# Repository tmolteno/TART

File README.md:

# Transient Array Radio Telescope

This repository has been ARCHIVED. It has been split into many smaller repositories under the tart-telescope organization.
see (https://github.com/tart-telescope) for details

The [Transient Array Radio Telescope](https://en.wikipedia.org/wiki/Transient_Array_Radio_Telescope) (TART) is a low-cost 24-element aperture synthesis array
developed by the [Elec Research Group](http://elec.ac.nz) at the University of Otago

 ![All-sky image from a TART telescope][tart_image] 

The TART software and hardware designs are released as open-source designs and are
licensed under the GPL v3.

The authors of the first version of the TART are Tim Molteno, Charles Shaw, Max 
Scheel and Phil Brown. Enquries about the TART should be addressed to Tim Molteno (tim@elec.ac.nz). 

[Connect to our development radio telescope here](https://tart.elec.ac.nz "Online Telescopes")

## Hardware

The TART hardware is designed using a combination of KiCAD (newest boards) and
CadSoft's Eagle package. These designs are located in the [hardware](hardware/README.md) folder. 

## Firmware

The TART uses an FPGA to synchronize data from each receiver. The code for this in the 
Verilog language is in the [hardware/FPGA](hardware/FPGA/README.md) directory

## Installation

See the  [Installation Instructions](INSTALL.md) file for more detail on installation.

[tart_image]: https://github.com/tmolteno/TART/blob/master/doc/img/tart_image.jpg "TART All-Sky Image"

## Telescope API documentation

The [Telescope API documentation](https://tart.elec.ac.nz/doc/) describes how the TART is controlled via the network for configration and data retrieval.

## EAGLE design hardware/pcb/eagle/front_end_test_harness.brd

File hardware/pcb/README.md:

At the moment TART consists of three different PCBs:

1. (24x) Radio module (RF front end)
2. (4x) Radio hub module (jitter cleaner, power supply, 485 transceiver and base for 6 Radio modules)
3. (1x) Base station module (485 transceiver, oscillator, power supply, host for acquisition FPGA and Raspberry Pi)

base_station, radio_hub_module and radio_module are the original designs used for all currently built up TART's (as of Feb 2019). The base_station folder is a KIcad project, while radio_hub_module and radio_module are created in Eagle PCB.

The *201902 folder are the above converted and updated to KIcad 5 projects.

BOM html and CSV files are included. These are generated by the github.com:SchrodingersGat/KiBoM.git plugin.

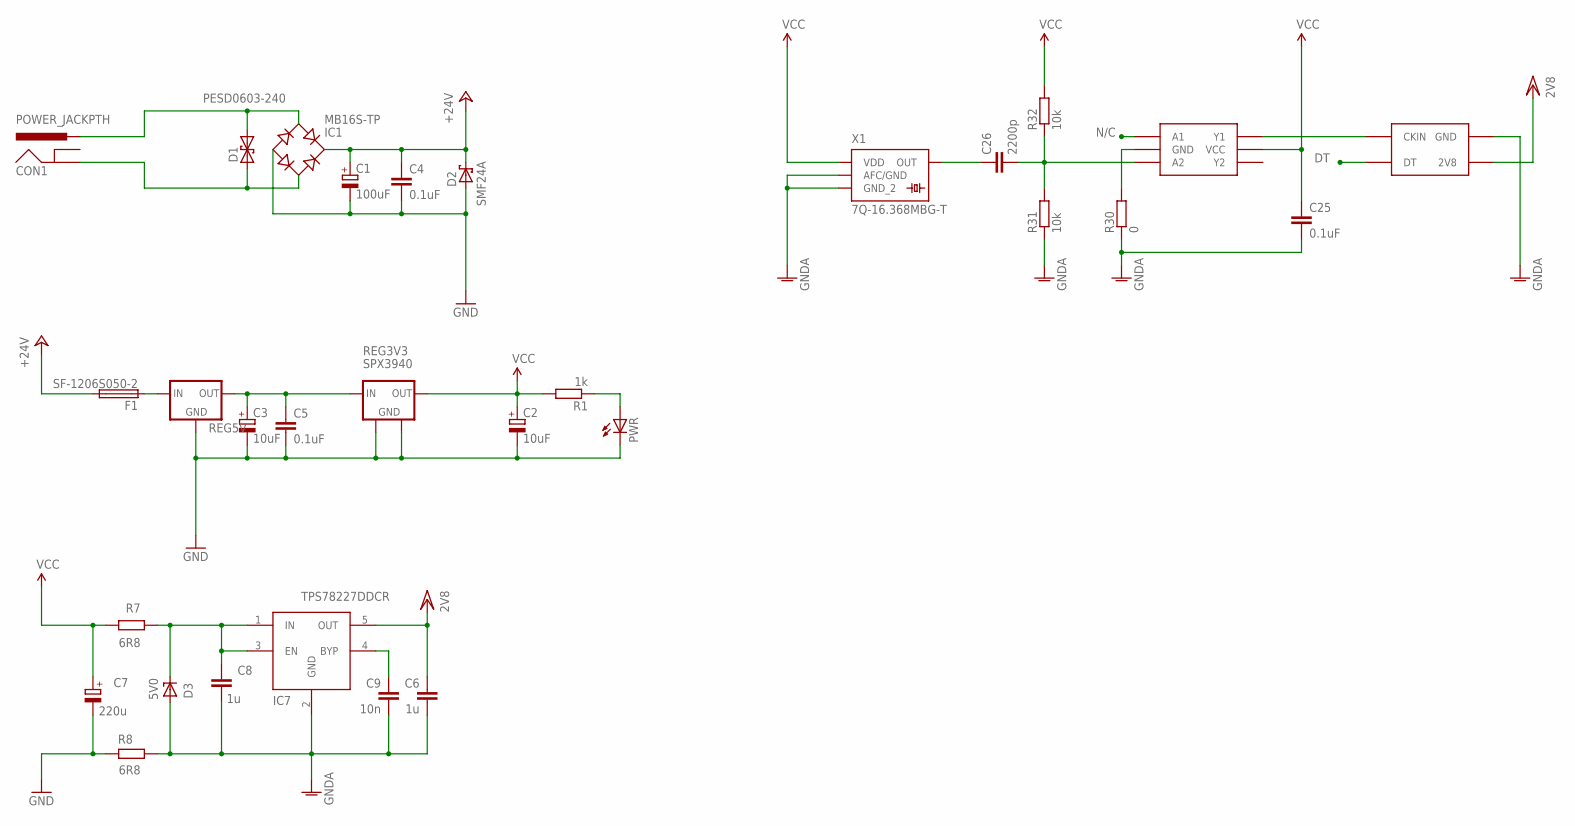
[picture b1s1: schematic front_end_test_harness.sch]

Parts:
C1: 100uF; E5-10,5
C2: 10uF; E2-5
C3: 10uF; E5-10,5
C4, C5: 0.1uF; C0805
C6, C8: 1u; C0603
C7: 220u; C1210
C9: 10n; C0603
C25: 0.1uF; C0603
C26: 2200p; C0603
CON1: POWER_JACKPTH; POWER_JACK_PTH
D1: PESD0603-240; D0603
D2: SMF24A; SOD123
D3: 5V0; SOD523
F1: SF-1206S050-2; F1206
IC1: MB16S-TP; SOIC-4
IC7: TPS78227DDCR; SOT23-5
IC26: NC7WZ16P6X
PWR: LEDCHIPLED_0805; CHIPLED_0805
R1: 1k; R0603
R7, R8: 6R8; R0805
R30: 0; R0603
R31, R32: 10k; R0603
REG3V3: SPX3940; SOT223
REG5V: V_REG_OKI-78SRSINK; TO220-IGO
U$2: TEST_HARNESS
X1: 7Q-16.368MBG-T; 4-SMD

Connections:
+2V8: C6.1, IC7.5 (OUT), U$2.2V8@11 (2V8), U$2.2V8@15 (2V8), U$2.2V8@16 (2V8)
+5V: C3.+, C5.1, REG3V3.1 (IN), REG5V.OUT
+24V: C1.+, C4.1, D2.C, F1.2, IC1.+
A2: C26.2, IC26.P$3 (A2), R31.2, R32.1
BYP: C9.1, IC7.4 (BYP)
CLK: IC26.P$6 (Y1), U$2.CKIN@13 (CKIN)
DT: U$2.DT@12 (DT)
GNDA: C6.2, C8.2, C9.2, C25.2, D3.A, IC7.2 (GND), R8.1, R30.1, R31.1, U$2.GND@1 (GND), U$2.GND@2 (GND), U$2.GND@3 (GND), U$2.GND@4 (GND), U$2.GND@5 (GND), U$2.GND@6 (GND), U$2.GND@7 (GND), U$2.GND@8 (GND), U$2.GND@9 (GND), U$2.GND@11 (GND), U$2.GND@14 (GND), X1.PAD_1 (AFC/GND), X1.PAD_2 (GND_2)
GNDINT: C1.-, C2.-, C3.-, C4.2, C5.2, C7.2 (-), D2.A, IC1.-, PWR.C, R8.2, REG3V3.2 (GND), REG3V3.4 (GND), REG5V.GND
unnamed: PWR.A, R1.1
unnamed: F1.1, REG5V.IN
unnamed: IC26.P$2 (GND), R30.2
unnamed: CON1.PWR, D1.2, IC1.~1 (AC1)
unnamed: CON1.GND, D1.1, IC1.~2 (AC2)
unnamed: C26.1, X1.PAD_3 (OUT)
N/C: IC26.P$1 (A1)
REG2V7IN: C8.1, D3.C, IC7.1 (IN), IC7.3 (EN), R7.1
VCC: C2.+, C7.1 (+), C25.1, IC26.P$5 (VCC), R1.2, R7.2, R32.2, REG3V3.3 (OUT), X1.PAD_4 (VDD)

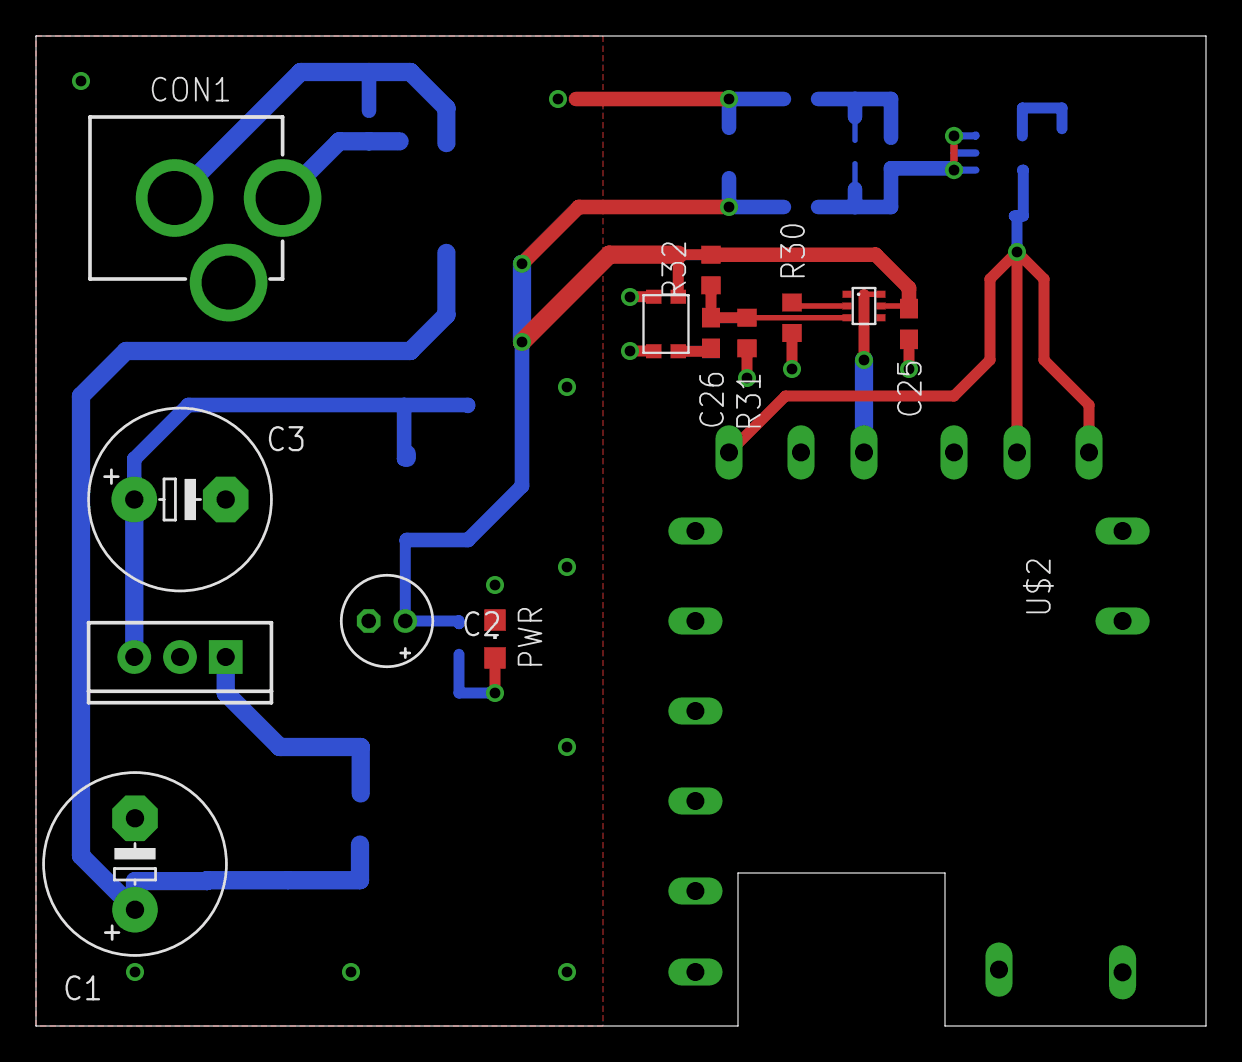
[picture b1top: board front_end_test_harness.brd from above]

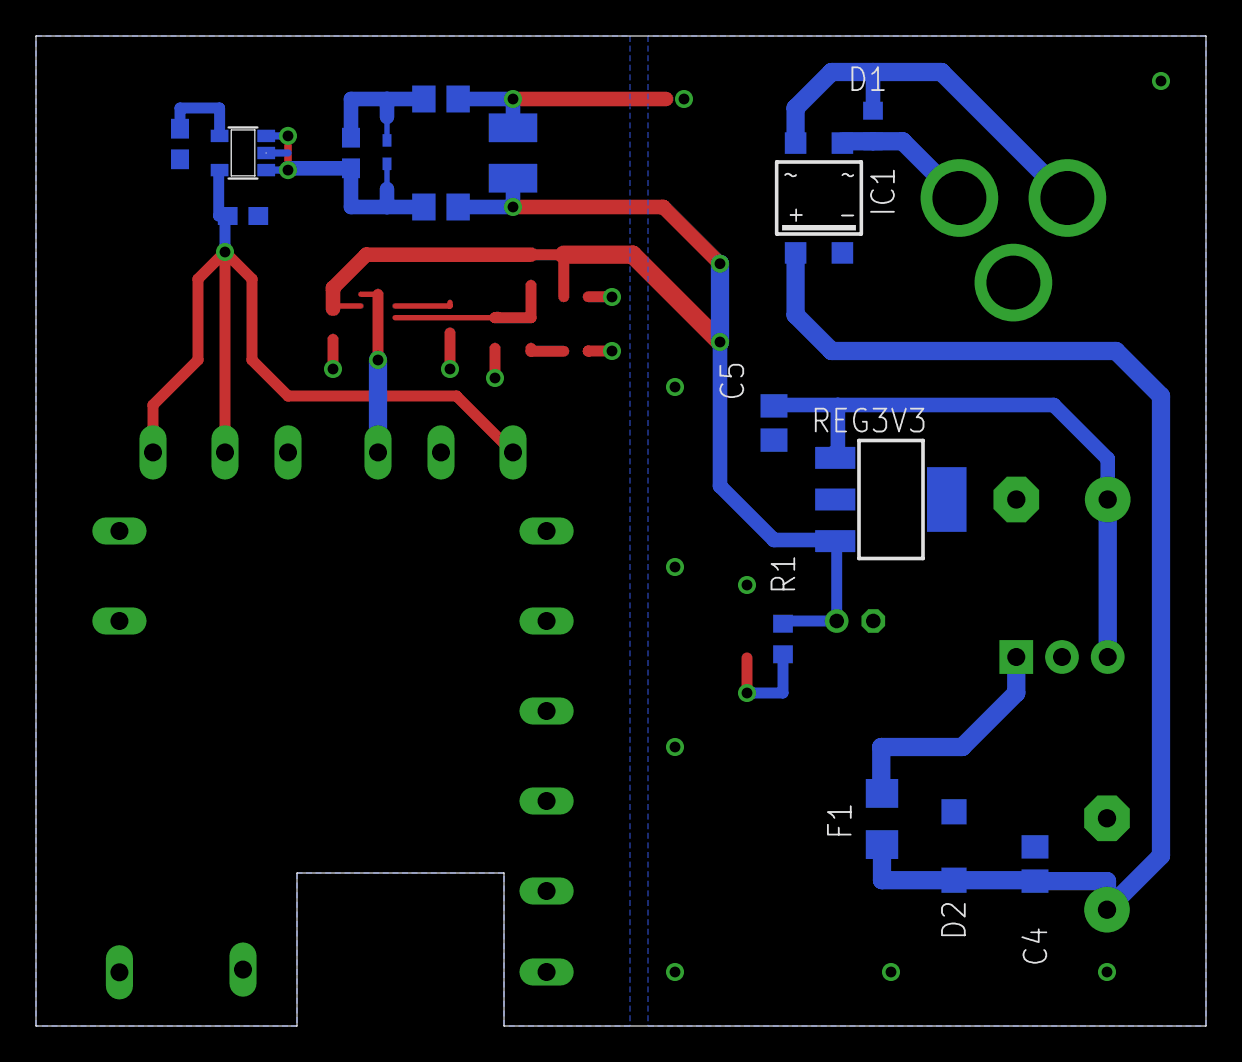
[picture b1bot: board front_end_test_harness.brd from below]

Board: 2 copper layers, 65.0 x 55.0 mm, 30 parts (16 on the bottom side), 16 nets.

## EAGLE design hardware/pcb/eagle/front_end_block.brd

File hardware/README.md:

# TART Hardware Description

The TART telescope consists of three major components.

* Radio Front End Module
* Radio Hub Module
* Base Station

## Radio Front End

The radio front end is a low-noise [radio](https://datasheets.maximintegrated.com/en/ds/MAX2769B.pdf) that digitizes the incoming signal at a sample rate of 16.368 MHz. An external clock input is used to synchronize the sampling. A full tart telescope consists of 24 radio front end modules arranged into four 'Tiles'

![TART GPS L1 radio front end][radio_front_end_image]

## Radio Hub Module

A radio hub module controls six radio front ends. It is responsible for generating low-noise power, 
and removing jitter from the main system clock (generated from the base station).
The radio hub distributes this clean clock to each of the radio front end modules. The data from each radio is converted to RS422 differential signaling and fed back down Cat-6 UTP cabling back to the basestation. 

![Radio Hub Module][radio_hub_image]

This image shows a radio hub with six radio front end modules mounted.

## Base Station

The basestation is responsible for three main tasks.

* Clock & Power Generation
* Data reception
* Data resynchronization and buffering
* Storage and Upload

The clock and power generation hardware is described in the pcb/base_station folder.

The data resynchronization and buffering is performed using an FPGA. The hardware and Verilog source for this are described
int the folder FPGA.

The Data storage and upload are managed by a raspberry pi computer running Linux. The software for operating this computer is described in the software directory in the main TART folder.

![Radio Telescope Basestation][basestation_image]

[radio_front_end_image]: https://github.com/tmolteno/TART/blob/master/doc/img/radio_module.png "TART Radio Module"
[radio_hub_image]: https://github.com/tmolteno/TART/blob/master/doc/img/radio_hub_photo.jpg "TART Radio Hub"
[basestation_image]: https://github.com/tmolteno/TART/blob/master/doc/img/control_board_photo.png "TART Basestation"

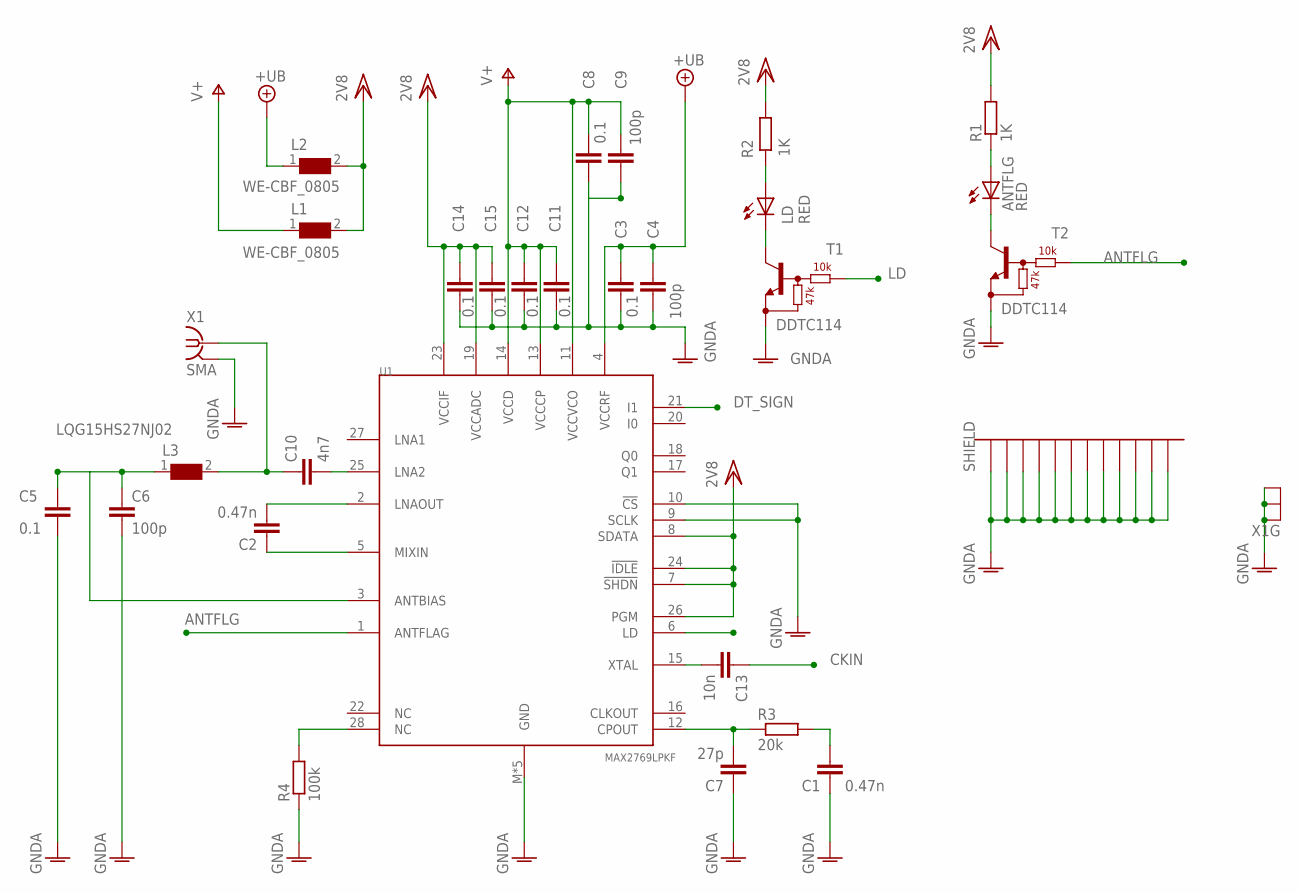
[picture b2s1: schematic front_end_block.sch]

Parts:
ANTFLG: RED; CHIP-LED0603
C1: 0.47n; C0603
C2: 0.47n; C0402
C3, C8, C11, C12, C15: 0.1; C0402
C4, C6, C9: 100p; C0402
C5, C14: 0.1; C0603
C7: 27p; C0402
C10: 4n7; C0402
C13: 10n; C0402
L1, L2: WE-CBF_0805; 0805
L3: LQG15HS27NJ02; 0402
LD: RED; CHIP-LED0603
R1, R2: 1K; R0402
R3: 20k; R0402
R4: 100k; R0402
S2: BMIS-202
T1, T2: DDTC114; SOT323-R_INFINEON
U1: MAX2769LPKF; QFN28LPKF
X1: SMA; J502-ND-142-0701-801/806

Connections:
+UB: C3.1, C4.1, L2.1, U1.4 (VCCRF)
ANTFLG: T2.1 (B), U1.1 (ANTFLAG)
CKIN: C13.1
DT_SIGN: U1.21 (I1)
GNDA: C1.1, C3.2, C4.2, C5.2, C6.2, C7.1, C8.2, C9.2, C11.2, C12.2, C14.2, C15.2, R4.1, S2.P$1, S2.P$2, S2.P$3, S2.P$4, S2.P$5, S2.P$6, S2.P$7, S2.P$8, S2.P$9, S2.P$10, S2.P$11, S2.P$12, T1.2 (E), T2.2 (E), U1.9 (SCLK), U1.10 (!CS), U1.M (GND), U1.P$4 (GND), U1.P$6 (GND), U1.P$7 (GND), U1.P$9 (GND), X1.G@1 (GND), X1.G@2 (GND), X1.G@3 (GND), X1.G@4 (GND)
LD: T1.1 (B), U1.6 (LD)
LNA2: C10.2, U1.25 (LNA2)
LNAOUT: C2.2, U1.2 (LNAOUT)
MIXIN: C2.1, U1.5 (MIXIN)
unnamed: C7.2, R3.1, U1.12 (CPOUT)
unnamed: C1.2, R3.2
unnamed: C5.1, C6.1, L3.1, U1.3 (ANTBIAS)
unnamed: ANTFLG.A, R1.1
unnamed: ANTFLG.C, T2.3 (C)
unnamed: LD.A, R2.1
unnamed: LD.C, T1.3 (C)
unnamed: R4.2, U1.28 (NC)
unnamed: C10.1, L3.2, X1.1
V+: C8.1, C9.1, C11.1, C12.1, L1.1, U1.11 (VCCVCO), U1.13 (VCCCP), U1.14 (VCCD)
VCC/2: C14.1, C15.1, L1.2, L2.2, R1.2, R2.2, U1.7 (!SHDN), U1.8 (SDATA), U1.19 (VCCADC), U1.23 (VCCIF), U1.24 (!IDLE), U1.26 (PGM)
XTAL: C13.2, U1.15 (XTAL)

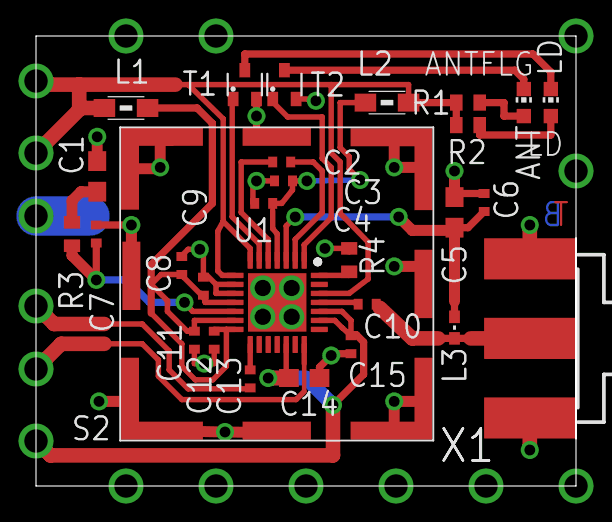
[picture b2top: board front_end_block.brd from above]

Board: 2 copper layers, 30.0 x 25.0 mm, 29 parts (0 on the bottom side), 19 nets.

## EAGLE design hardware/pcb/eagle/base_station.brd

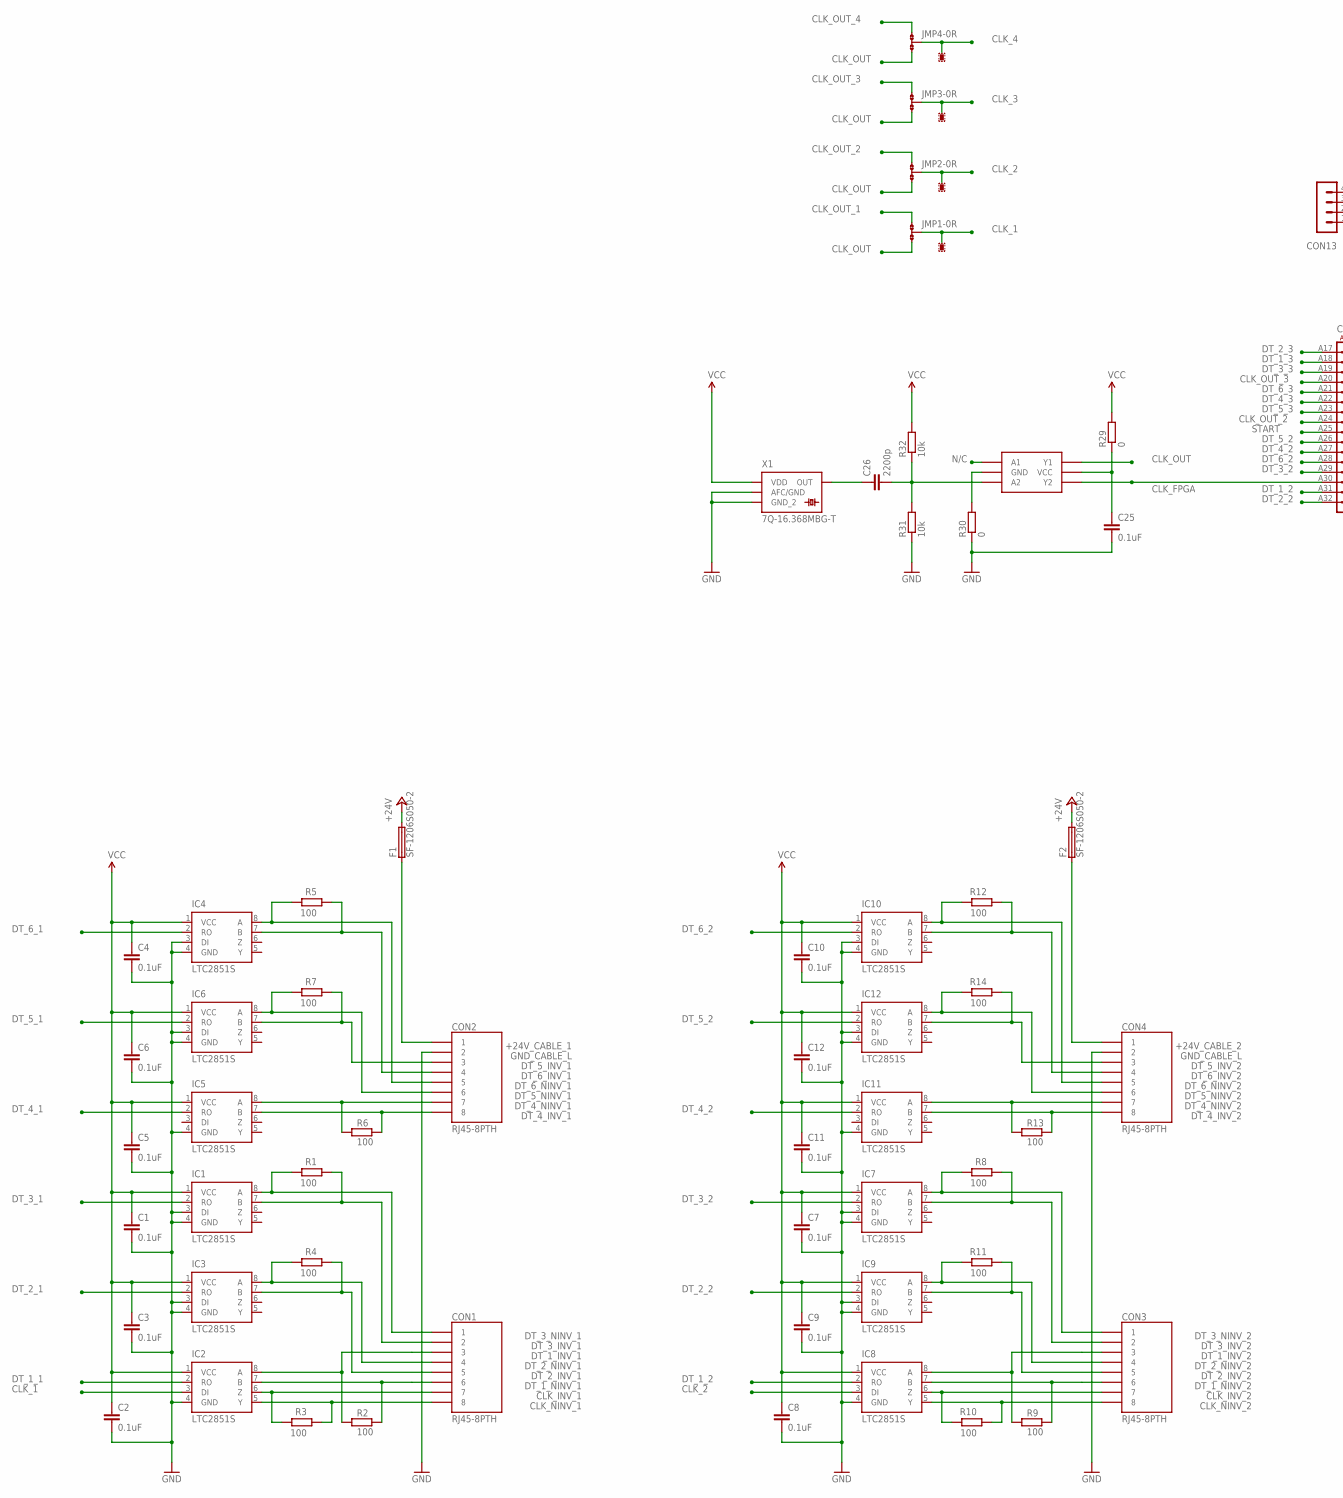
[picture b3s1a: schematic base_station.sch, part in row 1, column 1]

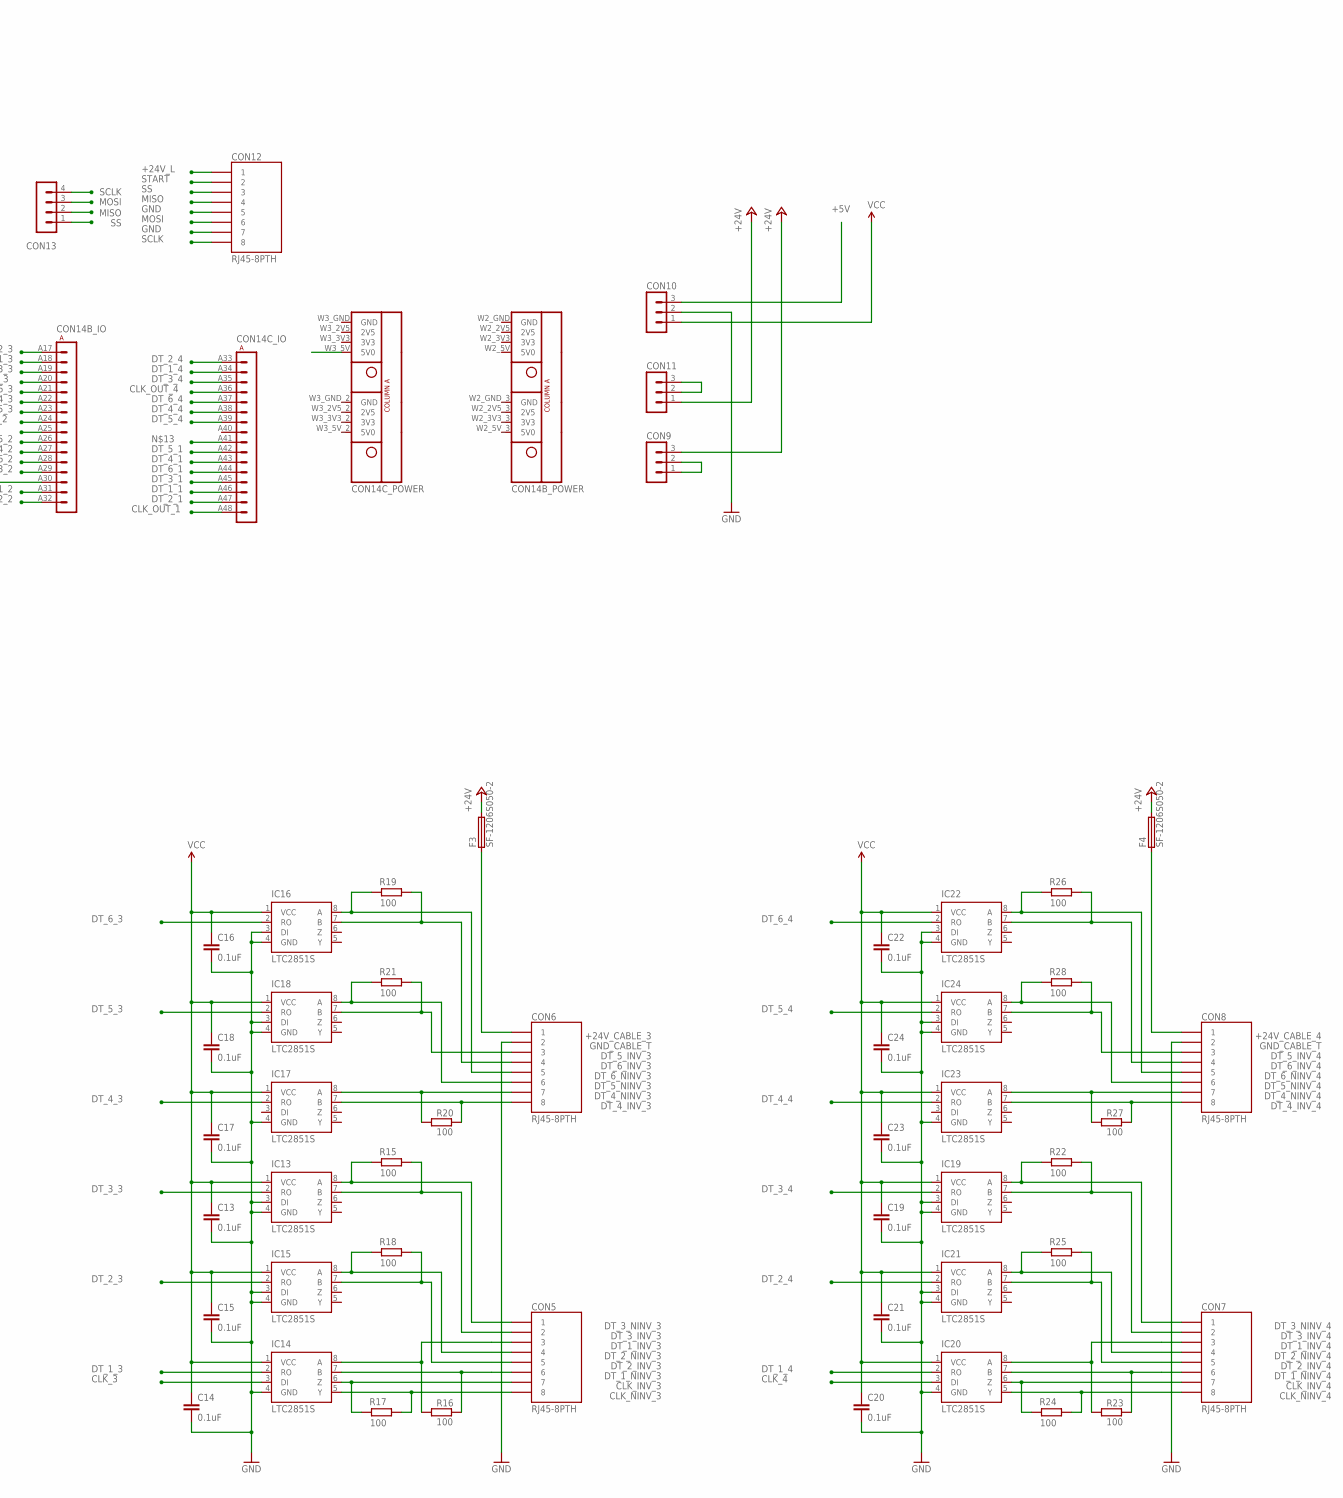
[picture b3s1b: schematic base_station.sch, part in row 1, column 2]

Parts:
C1, C2, C3, C4, C5, C6, C7, C8, C9, C10, C11, C12, C13, C14, C15, C16, C17, C18, C19, C20, C21, C22, C23, C24, C25: 0.1uF; C0603
C26: 2200p; C0603
CON1, CON2, CON3, CON4, CON5, CON6, CON7, CON8, CON12: RJ45-8PTH; RJ45-8
CON9, CON10, CON11: MA03-1
CON13: WING4; WINGSIDE_4BIT
CON14: MEGAWING_HALF_P1; MEGAWING_HALF_NOHOLES_P1
F1, F2, F3, F4: SF-1206S050-2; F1206
IC1, IC2, IC3, IC4, IC5, IC6, IC7, IC8, IC9, IC10, IC11, IC12, IC13, IC14, IC15, IC16, IC17, IC18, IC19, IC20, IC21, IC22, IC23, IC24: LTC2851S; SOIC8
IC26: NC7WZ16P6X
JMP1, JMP2, JMP3, JMP4: 0R-JUMPA; A0R-JMP
R1, R2, R3, R4, R5, R6, R7, R8, R9, R10, R11, R12, R13, R14, R15, R16, R17, R18, R19, R20, R21, R22, R23, R24, R25, R26, R27, R28: 100; R0603
R29, R30: 0; R0603
R31, R32: 10k; R0603
X1: 7Q-16.368MBG-T; 4-SMD

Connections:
+5V: CON10.3, CON14.W3_5V (5V0)
+24V_CABLE_1: CON2.1, F1.1
+24V_CABLE_2: CON4.1, F2.1
+24V_CABLE_3: CON6.1, F3.1
+24V_CABLE_4: CON8.1, F4.1
+24V_L: CON9.3, CON12.1, F1.2, F2.2
+24V_T: CON11.1, F3.2, F4.2
CLK_1: IC2.3 (DI), JMP1.2
CLK_2: IC8.3 (DI), JMP2.2
CLK_3: IC14.3 (DI), JMP3.2
CLK_4: IC20.3 (DI), JMP4.2
CLK_FPGA: CON14.A30 (A14), IC26.P$4 (Y2)
CLK_INV_1: CON1.7, IC2.6 (Z), R3.2
CLK_INV_2: CON3.7, IC8.6 (Z), R10.2
CLK_INV_3: CON5.7, IC14.6 (Z), R17.2
CLK_INV_4: CON7.7, IC20.6 (Z), R24.2
CLK_NINV_1: CON1.8, IC2.5 (Y), R3.1
CLK_NINV_2: CON3.8, IC8.5 (Y), R10.1
CLK_NINV_3: CON5.8, IC14.5 (Y), R17.1
CLK_NINV_4: CON7.8, IC20.5 (Y), R24.1
CLK_OUT: IC26.P$6 (Y1), JMP1.3, JMP2.3, JMP3.3, JMP4.3
CLK_OUT_1: CON14.A48 (A16), JMP1.1
CLK_OUT_2: CON14.A24 (A8), JMP2.1
CLK_OUT_3: CON14.A20 (A4), JMP3.1
CLK_OUT_4: CON14.A36 (A4), JMP4.1
DT_1_1: CON14.A46 (A14), IC2.2 (RO)
DT_1_2: CON14.A31 (A15), IC8.2 (RO)
DT_1_3: CON14.A18 (A2), IC14.2 (RO)
DT_1_4: CON14.A34 (A2), IC20.2 (RO)
DT_1_INV_1: CON1.3, IC2.8 (A), R2.1
DT_1_INV_2: CON3.3, IC8.8 (A), R9.1
DT_1_INV_3: CON5.3, IC14.8 (A), R16.1
DT_1_INV_4: CON7.3, IC20.8 (A), R23.1
DT_1_NINV_1: CON1.6, IC2.7 (B), R2.2
DT_1_NINV_2: CON3.6, IC8.7 (B), R9.2
DT_1_NINV_3: CON5.6, IC14.7 (B), R16.2
DT_1_NINV_4: CON7.6, IC20.7 (B), R23.2
DT_2_1: CON14.A47 (A15), IC3.2 (RO)
DT_2_2: CON14.A32 (A16), IC9.2 (RO)
DT_2_3: CON14.A17 (A1), IC15.2 (RO)
DT_2_4: CON14.A33 (A1), IC21.2 (RO)
DT_2_INV_1: CON1.5, IC3.7 (B), R4.1
DT_2_INV_2: CON3.5, IC9.7 (B), R11.1
DT_2_INV_3: CON5.5, IC15.7 (B), R18.1
DT_2_INV_4: CON7.5, IC21.7 (B), R25.1
DT_2_NINV_1: CON1.4, IC3.8 (A), R4.2
DT_2_NINV_2: CON3.4, IC9.8 (A), R11.2
DT_2_NINV_3: CON5.4, IC15.8 (A), R18.2
DT_2_NINV_4: CON7.4, IC21.8 (A), R25.2
DT_3_1: CON14.A45 (A13), IC1.2 (RO)
DT_3_2: CON14.A29 (A13), IC7.2 (RO)
DT_3_3: CON14.A19 (A3), IC13.2 (RO)
DT_3_4: CON14.A35 (A3), IC19.2 (RO)
DT_3_INV_1: CON1.2, IC1.7 (B), R1.1
DT_3_INV_2: CON3.2, IC7.7 (B), R8.1
DT_3_INV_3: CON5.2, IC13.7 (B), R15.1
DT_3_INV_4: CON7.2, IC19.7 (B), R22.1
DT_3_NINV_1: CON1.1, IC1.8 (A), R1.2
DT_3_NINV_2: CON3.1, IC7.8 (A), R8.2
DT_3_NINV_3: CON5.1, IC13.8 (A), R15.2
DT_3_NINV_4: CON7.1, IC19.8 (A), R22.2
DT_4_1: CON14.A43 (A11), IC5.2 (RO)
DT_4_2: CON14.A27 (A11), IC11.2 (RO)
DT_4_3: CON14.A22 (A6), IC17.2 (RO)
DT_4_4: CON14.A38 (A6), IC23.2 (RO)
DT_4_INV_1: CON2.8, IC5.7 (B), R6.2
DT_4_INV_2: CON4.8, IC11.7 (B), R13.2
DT_4_INV_3: CON6.8, IC17.7 (B), R20.2
DT_4_INV_4: CON8.8, IC23.7 (B), R27.2
DT_4_NINV_1: CON2.7, IC5.8 (A), R6.1
DT_4_NINV_2: CON4.7, IC11.8 (A), R13.1
DT_4_NINV_3: CON6.7, IC17.8 (A), R20.1
DT_4_NINV_4: CON8.7, IC23.8 (A), R27.1
DT_5_1: CON14.A42 (A10), IC6.2 (RO)
DT_5_2: CON14.A26 (A10), IC12.2 (RO)
DT_5_3: CON14.A23 (A7), IC18.2 (RO)
DT_5_4: CON14.A39 (A7), IC24.2 (RO)
DT_5_INV_1: CON2.3, IC6.7 (B), R7.1
DT_5_INV_2: CON4.3, IC12.7 (B), R14.1
DT_5_INV_3: CON6.3, IC18.7 (B), R21.1
DT_5_INV_4: CON8.3, IC24.7 (B), R28.1
DT_5_NINV_1: CON2.6, IC6.8 (A), R7.2
DT_5_NINV_2: CON4.6, IC12.8 (A), R14.2
DT_5_NINV_3: CON6.6, IC18.8 (A), R21.2
DT_5_NINV_4: CON8.6, IC24.8 (A), R28.2
DT_6_1: CON14.A44 (A12), IC4.2 (RO)
DT_6_2: CON14.A28 (A12), IC10.2 (RO)
DT_6_3: CON14.A21 (A5), IC16.2 (RO)
DT_6_4: CON14.A37 (A5), IC22.2 (RO)
DT_6_INV_1: CON2.4, IC4.7 (B), R5.1
DT_6_INV_2: CON4.4, IC10.7 (B), R12.1
DT_6_INV_3: CON6.4, IC16.7 (B), R19.1
DT_6_INV_4: CON8.4, IC22.7 (B), R26.1
DT_6_NINV_1: CON2.5, IC4.8 (A), R5.2
DT_6_NINV_2: CON4.5, IC10.8 (A), R12.2
DT_6_NINV_3: CON6.5, IC16.8 (A), R19.2
DT_6_NINV_4: CON8.5, IC22.8 (A), R26.2
GND: C1.2, C2.2, C3.2, C4.2, C5.2, C6.2, C7.2, C8.2, C9.2, C10.2, C11.2, C12.2, C13.2, C14.2, C15.2, C16.2, C17.2, C18.2, C19.2, C20.2, C21.2, C22.2, C23.2, C24.2, C25.2, CON10.2, CON12.5, CON12.7, CON14.W2_GND (GND), CON14.W2_GND_3 (GND), CON14.W3_GND (GND), CON14.W3_GND_2 (GND), IC1.3 (DI), IC1.4 (GND), IC2.4 (GND), IC3.3 (DI), IC3.4 (GND), IC4.3 (DI), IC4.4 (GND), IC5.4 (GND), IC6.3 (DI), IC6.4 (GND), IC7.3 (DI), IC7.4 (GND), IC8.4 (GND), IC9.3 (DI), IC9.4 (GND), IC10.3 (DI), IC10.4 (GND), IC11.4 (GND), IC12.3 (DI), IC12.4 (GND), IC13.3 (DI), IC13.4 (GND), IC14.4 (GND), IC15.3 (DI), IC15.4 (GND), IC16.3 (DI), IC16.4 (GND), IC17.4 (GND), IC18.3 (DI), IC18.4 (GND), IC19.3 (DI), IC19.4 (GND), IC20.4 (GND), IC21.3 (DI), IC21.4 (GND), IC22.3 (DI), IC22.4 (GND), IC23.4 (GND), IC24.3 (DI), IC24.4 (GND), R30.1, R31.1, X1.PAD_1 (AFC/GND), X1.PAD_2 (GND_2)
GND_CABLE_L: CON2.2, CON4.2, CON9.1, CON9.2
GND_CABLE_T: CON6.2, CON8.2, CON11.2, CON11.3
MISO: CON12.4, CON13.2 (A2)
MOSI: CON12.6, CON13.3 (A3)
unnamed: IC26.P$2 (GND), R30.2
unnamed: C25.1, IC26.P$5 (VCC), R29.1
unnamed: C26.2, IC26.P$3 (A2), R31.2, R32.1
unnamed: C26.1, X1.PAD_3 (OUT)
N/C: IC26.P$1 (A1)
SCLK: CON12.8, CON13.4 (A4)
SS: CON12.3, CON13.1 (A1)
START: CON12.2, CON14.A25 (A9)
VCC: C1.1, C2.1, C3.1, C4.1, C5.1, C6.1, C7.1, C8.1, C9.1, C10.1, C11.1, C12.1, C13.1, C14.1, C15.1, C16.1, C17.1, C18.1, C19.1, C20.1, C21.1, C22.1, C23.1, C24.1, CON10.1, IC1.1 (VCC), IC2.1 (VCC), IC3.1 (VCC), IC4.1 (VCC), IC5.1 (VCC), IC6.1 (VCC), IC7.1 (VCC), IC8.1 (VCC), IC9.1 (VCC), IC10.1 (VCC), IC11.1 (VCC), IC12.1 (VCC), IC13.1 (VCC), IC14.1 (VCC), IC15.1 (VCC), IC16.1 (VCC), IC17.1 (VCC), IC18.1 (VCC), IC19.1 (VCC), IC20.1 (VCC), IC21.1 (VCC), IC22.1 (VCC), IC23.1 (VCC), IC24.1 (VCC), R29.2, R32.2, X1.PAD_4 (VDD)

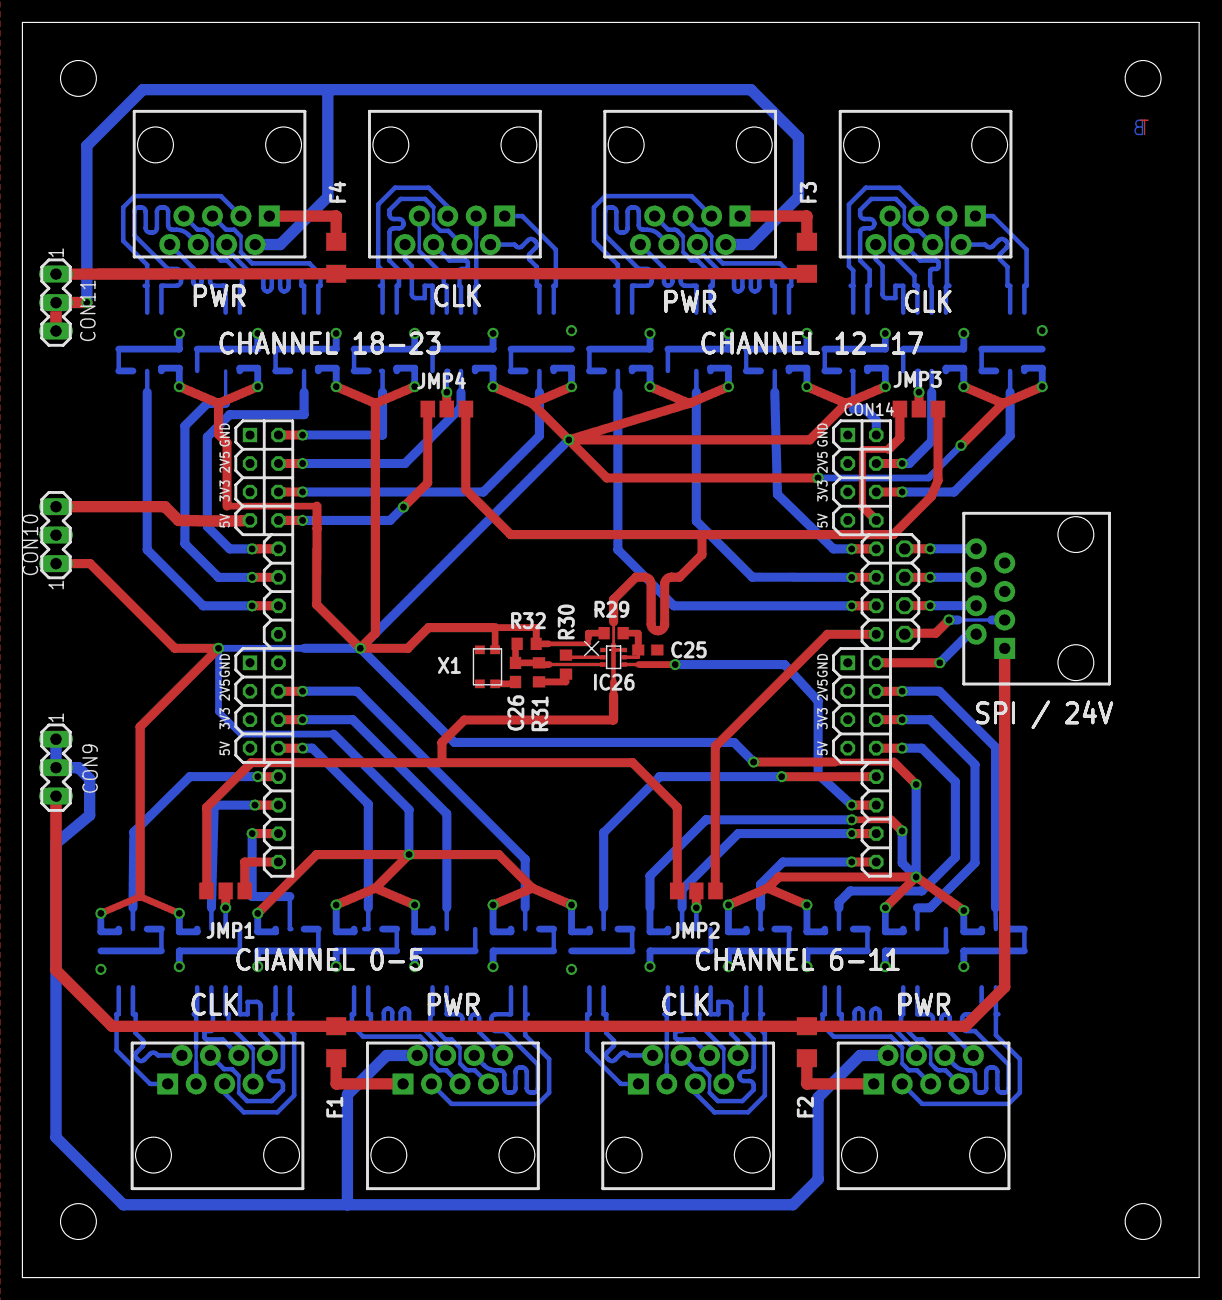
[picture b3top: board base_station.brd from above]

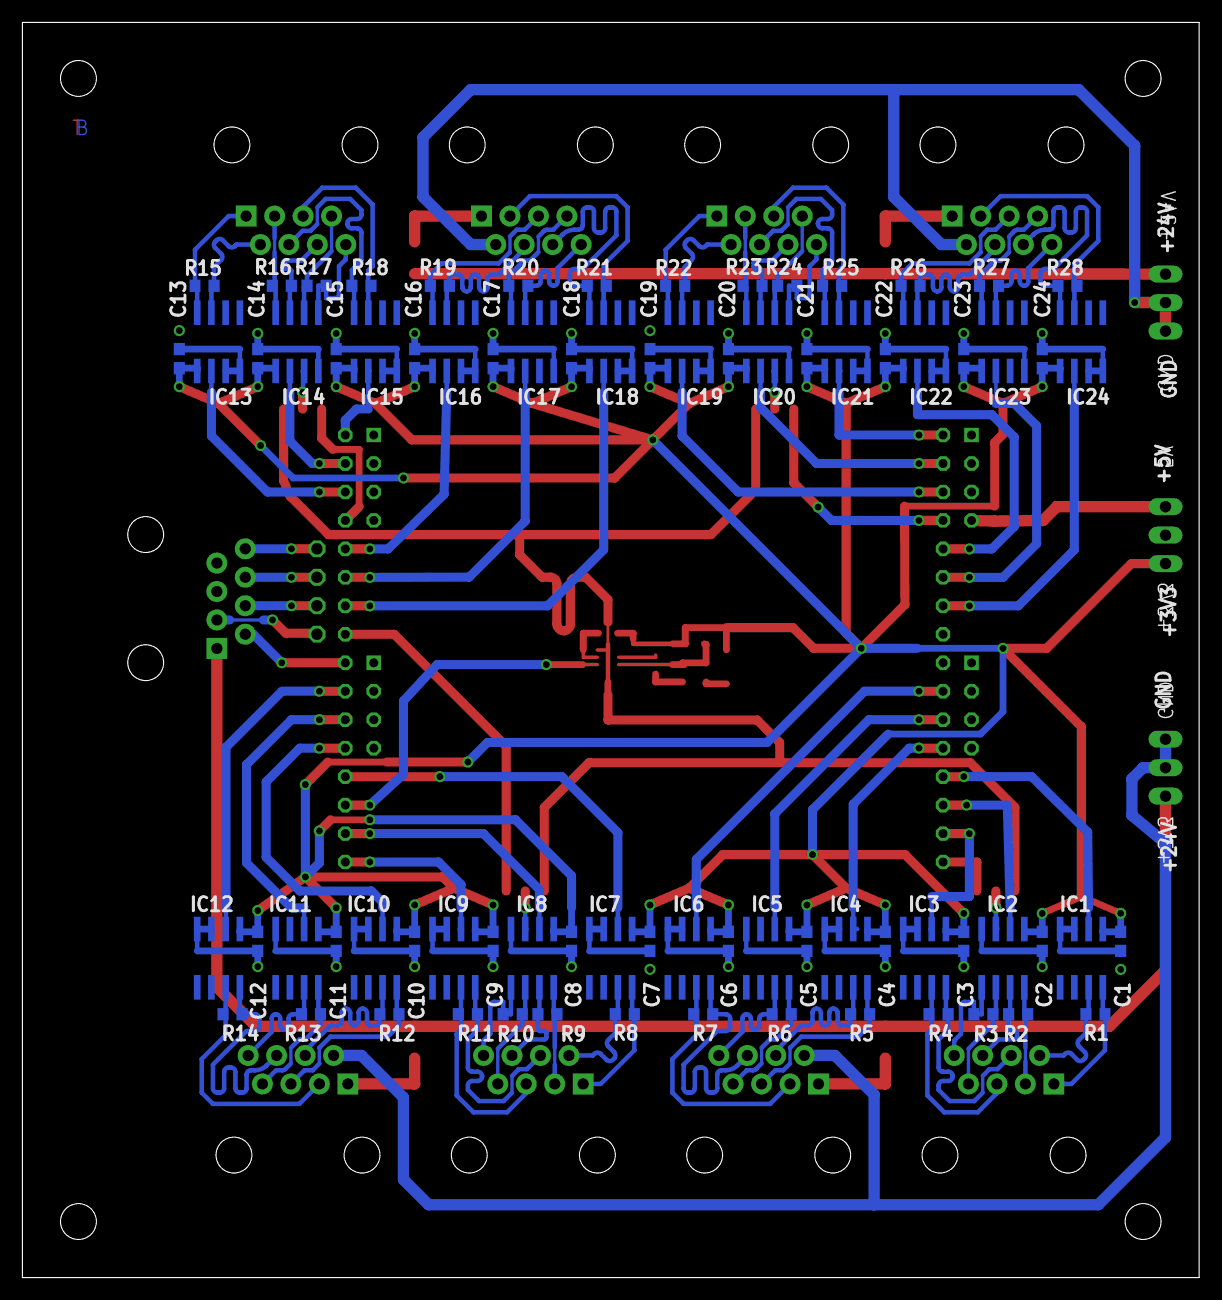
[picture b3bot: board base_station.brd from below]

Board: 2 copper layers, 105.0 x 112.0 mm, 106 parts (76 on the bottom side), 110 nets.

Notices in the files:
hardware/pcb/eagle/clk_module.brd:
(c)2014
TART clock module (c)2014
hardware/pcb/eagle/radio_module.brd:
TART radio module (c)2014
hardware/pcb/legacy/radio_hub_module/radio_hub_module.brd:
(c)2015
parts and their libraries:
wuerth_elektronik_eisos__v6.12: Copyright: Würth Elektronik
